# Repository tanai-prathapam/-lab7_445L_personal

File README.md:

## 0 Repository Structure

The typical explanation for the repo structure. Lab specific instructions can be
found further below.

### 0.1 HW

The `hw` folder should contain your schematic and board files for your PCB or
circuits. The ECE445L_Lab7 is the shared KiCad schematic for this lab and the final project (lab 10). 

### 0.2 SW

The `sw` folder should contain your application firmware and software written
for the lab. The `sw/inc` folder contains firmware drivers written for you by
Professor Valvano. Feel free to write your own (in fact, in some labs, you may
be required to write your own).

You can place any other source files in the `sw` folder. TAs will look at the
files you create and/or modify for software quality and for running your
project.

### 0.3 Resources

A couple files are provided in the Resources folder so you don't have to keep
searching for that one TI document. Some of them are immediately useful, like
the MSPM0 datasheet.

### 0.4 Git and Github

We will extensively use Git and Github for managing lab projects. This makes it
easier for TAs to grade and help debug the project by allowing us to see commit
histories, maintain a common project structure, and likewise, it makes it easier
for students to collaborate with partners, merge different codebases, and to
debug their work by having a history of commits.

Two common ways of using Git and Github are [Github Desktop](https://desktop.github.com/) and the [command line](https://git-scm.com/downloads).
[Tutorials](https://dev.to/mollynem/git-github--workflow-fundamentals-5496) are also abundant on the net for you to peruse. We've provided a cheatsheet for git
in the Resources folder.

It is highly recommended to make the most out of Git, even if you've never used
it before. Version control will save you a lot of suffering, and tools like Git
or SVN are ubiquitous in the industry.

A gitignore file is added to the root of this repo that may prevent specific
files from being tagged to the repo. This are typically autogenerated output
files we don't care about, but sometimes other stuff (like .lib files) falls
through that we want. Feel free to modify if necessary.

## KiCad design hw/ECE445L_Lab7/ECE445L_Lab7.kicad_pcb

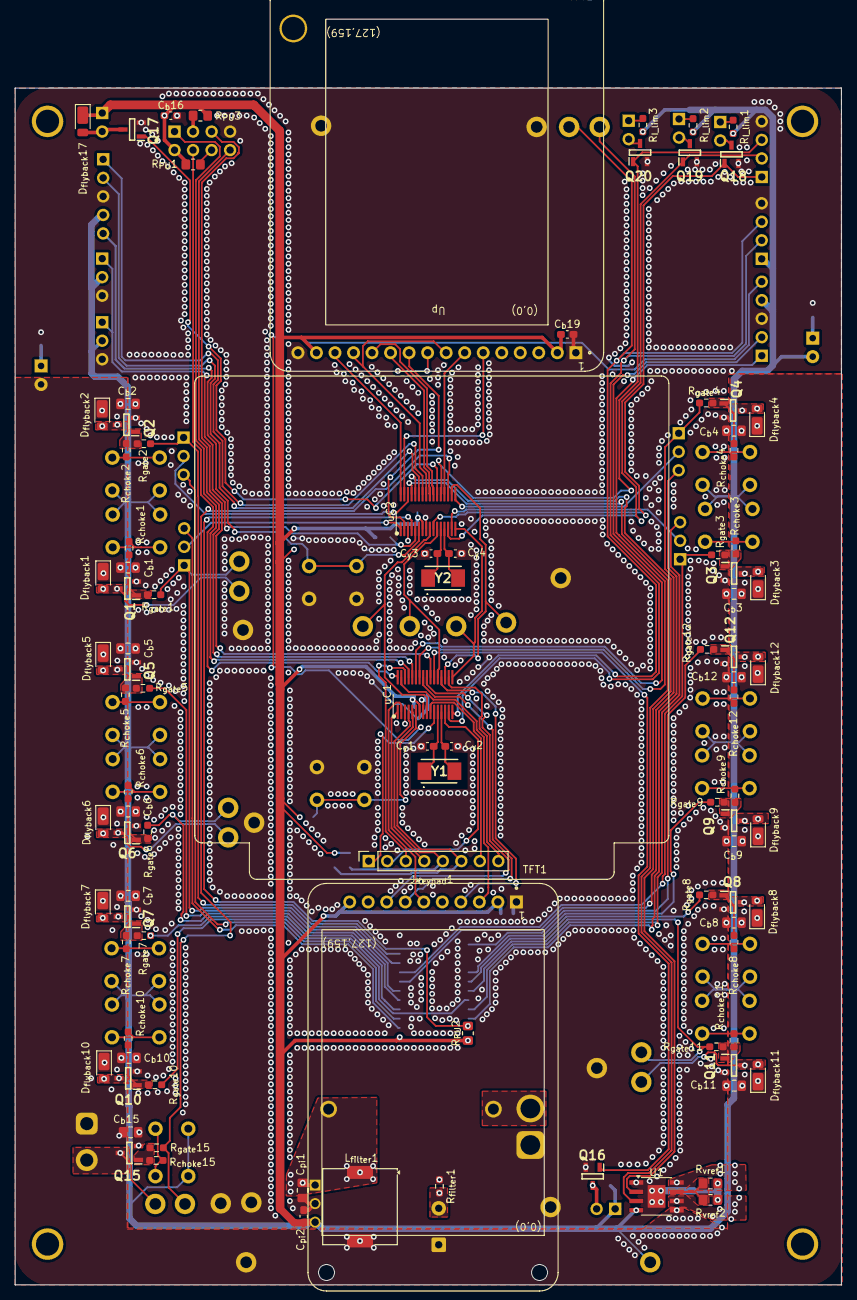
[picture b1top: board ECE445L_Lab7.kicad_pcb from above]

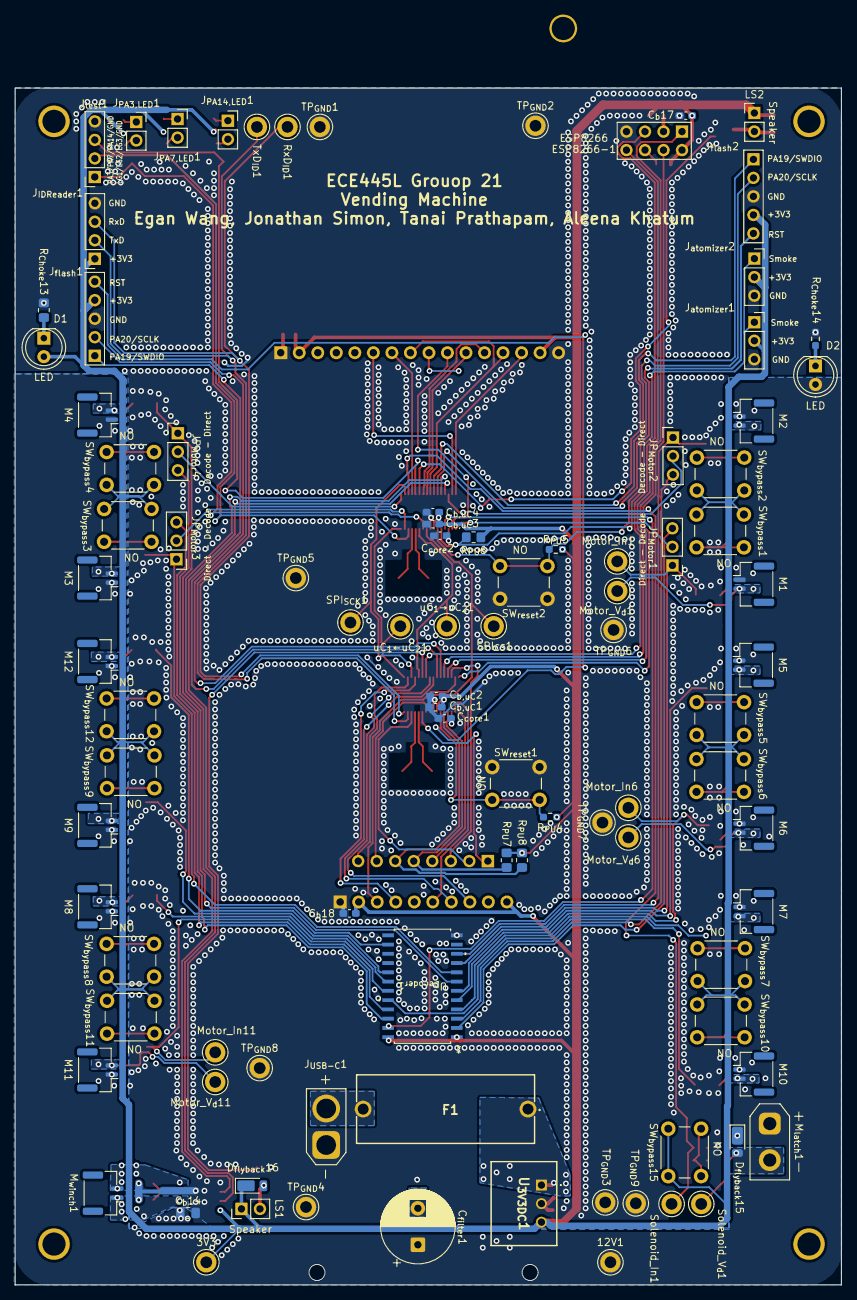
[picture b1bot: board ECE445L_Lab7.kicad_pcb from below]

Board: 2 copper layers, 113.3 x 164.1 mm, 195 parts (95 on the bottom side), 132 nets.

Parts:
3V3, 12V1: TestPoint; TestPoint_Keystone_5010-5014_Multipurpose
C_{b,uC}1, C_{b,uC}3: 100n; C_0603_1608Metric_Pad1.08x0.95mm_HandSolder
C_{b,uC}2, C_{b,uC}4: 10u; C_0603_1608Metric_Pad1.08x0.95mm_HandSolder
C_{b}1, C_{b}2, C_{b}3, C_{b}4, C_{b}5, C_{b}6, C_{b}7, C_{b}8, C_{b}9, C_{b}10, C_{b}11, C_{b}12, C_{b}14, C_{b}15: 4.7u; C_0805_2012Metric_Pad1.18x1.45mm_HandSolder
C_{b}16: 100n; C_0603_1608Metric_Pad1.08x0.95mm_HandSolder
C_{b}17, C_{b}18, C_{b}19: 4.7u; C_0603_1608Metric_Pad1.08x0.95mm_HandSolder
C_{core}1, C_{core}2: 0.47u; C_0603_1608Metric_Pad1.08x0.95mm_HandSolder
C_{filter}1: 1200u; CP_Radial_D10.0mm_P5.00mm
C_{pi}1: 4.7u; C_0805_2012Metric_Pad1.18x1.45mm_HandSolder
C_{pi}2: 4.7u; C_0603_1608Metric_Pad1.08x0.95mm_HandSolder
C_{y}1, C_{y}2, C_{y}3, C_{y}4: 10p; C_0603_1608Metric_Pad1.08x0.95mm_HandSolder
D1, D2: LED; LED_D5.0mm
D_{flyback}1, D_{flyback}2, D_{flyback}3, D_{flyback}4, D_{flyback}5, D_{flyback}6, D_{flyback}7, D_{flyback}8, D_{flyback}9, D_{flyback}10, D_{flyback}11, D_{flyback}12, D_{flyback}15, D_{flyback}16, D_{flyback}17: DFLS240LX-7; D_PowerDI-123
ESP8266: ESP8266-1; PinHeader_2x04_P2.54mm_Vertical
F1: Fuse; WR-FSH_THT_2
H1, H2, H3, H4: MountingHole_4_40
JP_{Motor}1, JP_{Motor}2, JP_{Motor}3, JP_{Motor}4: Jumper_3_Open; PinHeader_1x03_P2.54mm_Vertical
J_{IDReader}1: Conn_01x04; PinSocket_1x04_P2.54mm_Vertical
J_{Keypad}1: Conn_01x08; 4x4_Matrix_Keypad
J_{PA3,LED}1, J_{PA7,LED}1, J_{PA14,LED}1: Conn_01x02; PinSocket_1x02_P2.54mm_Vertical
J_{USB-C}1: Conn_01x02; AMASS_XT30U-M_1x02_P5.0mm_Vertical
J_{atomizer}1, J_{atomizer}2: Conn_01x03; PinSocket_1x03_P2.54mm_Vertical
J_{flash}1: J_{flash}1; PinHeader_1x05_P2.54mm_Vertical
J_{flash}2: J_{flash}2; PinHeader_1x05_P2.54mm_Vertical
J_{test}1: Conn_02x04_Counter_Clockwise; PinSocket_1x04_P2.54mm_Vertical
LS1, LS2: Speaker; PinHeader_1x02_P2.54mm_Vertical
L_{filter}1: 10uH; L_Coilcraft_MSS1038-XXX
M1, M2, M3, M4, M5, M6, M7, M8, M9, M10, M11, M12: Motor_DC; JST_GH_BM02B-GHS-TBT_1x02-1MP_P1.25mm_Vertical
M_{latch}1: Solenoid; AMASS_XT30UPB-F_1x02_P5.0mm_Vertical
M_{winch}1: Motor_DC; JST_GH_BM02B-GHS-TBT_1x02-1MP_P1.25mm_Vertical
Motor_In1, Motor_In6, Motor_In11: TestPoint; TestPoint_Keystone_5010-5014_Multipurpose
Motor_V_{d}1, Motor_V_{d}6, Motor_V_{d}11: TestPoint; TestPoint_Keystone_5010-5014_Multipurpose
Q1, Q2, Q3, Q4, Q5, Q6, Q7, Q8, Q9, Q10, Q11, Q12, Q15, Q16, Q17, Q18, Q19, Q20: NTR4501NT1G; SOT96P237X111-3N
R_{Choke}13: 10k; R_0805_2012Metric_Pad1.20x1.40mm_HandSolder
R_{Choke}14: 36.5k; R_0603_1608Metric_Pad0.98x0.95mm_HandSolder
R_{I_lim}1, R_{I_lim}2, R_{I_lim}3: R; R_0603_1608Metric_Pad0.98x0.95mm_HandSolder
R_{PU}1, R_{PU}2, R_{PU}3, R_{PU}6, R_{PU}7, R_{PU}8: 10k; R_0805_2012Metric_Pad1.20x1.40mm_HandSolder
R_{PU}4, R_{PU}5: 10k; R_0603_1608Metric_Pad0.98x0.95mm_HandSolder
R_{choke}1, R_{choke}2, R_{choke}3, R_{choke}4, R_{choke}5, R_{choke}6, R_{choke}7, R_{choke}8, R_{choke}9, R_{choke}10, R_{choke}11, R_{choke}12, R_{choke}15: 680; R_0603_1608Metric_Pad0.98x0.95mm_HandSolder
R_{filter}1: 0.25; R_0603_1608Metric_Pad0.98x0.95mm_HandSolder
R_{gate}1, R_{gate}2, R_{gate}3, R_{gate}4, R_{gate}5, R_{gate}6, R_{gate}7, R_{gate}8, R_{gate}9, R_{gate}10, R_{gate}11, R_{gate}12, R_{gate}15: 0.25; R_0603_1608Metric_Pad0.98x0.95mm_HandSolder
R_{vref}1, R_{vref}2: 264m; R_0805_2012Metric_Pad1.20x1.40mm_HandSolder
RxD_{ID}1: TestPoint; TestPoint_Keystone_5010-5014_Multipurpose
SPI_{CS}1: TestPoint; TestPoint_Keystone_5010-5014_Multipurpose
SPI_{SCK}1: TestPoint; TestPoint_Keystone_5010-5014_Multipurpose
SW_{bypass}1, SW_{bypass}2, SW_{bypass}3, SW_{bypass}4, SW_{bypass}5, SW_{bypass}6, SW_{bypass}7, SW_{bypass}8, SW_{bypass}9, SW_{bypass}10, SW_{bypass}11, SW_{bypass}12, SW_{bypass}15: NO; SW_PUSH_6mm
SW_{reset}1, SW_{reset}2: NO; SW_PUSH_6mm
Solenoid_In1: TestPoint; TestPoint_Keystone_5010-5014_Multipurpose
Solenoid_V_{d}1: TestPoint; TestPoint_Keystone_5010-5014_Multipurpose
TFT1: Adafruit ST7735R; adafruit_st7735r2
TFT2: HiLetGo_ST7735R; hiletgo_st7735r2
TP_{GND}1, TP_{GND}2, TP_{GND}3, TP_{GND}4, TP_{GND}5, TP_{GND}6, TP_{GND}7, TP_{GND}8, TP_{GND}9: TestPoint; TestPoint_Keystone_5010-5014_Multipurpose
TxD_{ID}1: TestPoint; TestPoint_Keystone_5010-5014_Multipurpose
U1: DRV8231ADSG; TI_SO-PowerPAD-8
U_{3V3DC}1: N7803-2C; N78032C
U_{Decoder}1: MC14514BDWR2G; SOIC-24WB_ONS
Y1, Y2: 16MHz; ABM3
uC1, uC2: M0G3507QDGS32RQ1; VSSOP_0.5mm_32pin_handsolder
uC_{1}←uC_{2}1, uC_{1}→uC_{2}1: TestPoint; TestPoint_Keystone_5010-5014_Multipurpose

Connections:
+3V3: 3V3.1 (1_1), C_{b,uC}1.1, C_{b,uC}2.1, C_{b,uC}3.1, C_{b,uC}4.1, C_{b}16.1, C_{b}17.1, C_{b}18.1, C_{b}19.1, C_{pi}2.1, D1.2 (A), D_{flyback}16.1 (K), D_{flyback}17.1 (K), ESP8266.8 (Vcc), J_{IDReader}1.1, J_{atomizer}1.2, J_{atomizer}2.2, J_{flash}1.4 (C), J_{flash}2.4 (C), LS1.1, LS2.1, R_{I_lim}1.1, R_{I_lim}2.1, R_{I_lim}3.1, R_{PU}1.1, R_{PU}2.1, R_{PU}3.1, R_{PU}4.1, R_{PU}5.1, R_{PU}6.1, R_{PU}7.1, R_{PU}8.1, SW_{bypass}1.1, SW_{bypass}2.1, SW_{bypass}3.1, SW_{bypass}4.1, SW_{bypass}5.1, SW_{bypass}6.1, SW_{bypass}7.1, SW_{bypass}8.1, SW_{bypass}9.1, SW_{bypass}10.1, SW_{bypass}11.1, SW_{bypass}12.1, SW_{bypass}15.1, TFT1.2 (VCC), TFT1.10 (LITE), TFT2.2 (VCC), TFT2.15 (LED+), U1.4 (VREF), U_{3V3DC}1.3 (Vout), U_{Decoder}1.1 (ST), U_{Decoder}1.24 (VDD), uC1.7 (VDD), uC2.7 (VDD)
+12V: 12V1.1 (1_1), C_{b}1.1, C_{b}2.1, C_{b}3.1, C_{b}4.1, C_{b}5.1, C_{b}6.1, C_{b}7.1, C_{b}8.1, C_{b}9.1, C_{b}10.1, C_{b}11.1, C_{b}12.1, C_{b}14.1, C_{b}15.1, C_{filter}1.1, D2.2 (A), D_{flyback}1.1 (K), D_{flyback}2.1 (K), D_{flyback}3.1 (K), D_{flyback}4.1 (K), D_{flyback}5.1 (K), D_{flyback}6.1 (K), D_{flyback}7.1 (K), D_{flyback}8.1 (K), D_{flyback}9.1 (K), D_{flyback}10.1 (K), D_{flyback}11.1 (K), D_{flyback}12.1 (K), D_{flyback}15.1 (K), L_{filter}1.2, M1.1 (+), M2.1 (+), M3.1 (+), M4.1 (+), M5.1 (+), M6.1 (+), M7.1 (+), M8.1 (+), M9.1 (+), M10.1 (+), M11.1 (+), M12.1 (+), M_{latch}1.1 (+), U1.5 (VM)
/Lab7 Electromech/V_{d,motor 1}: D_{flyback}1.2 (A), M1.2 (-), Motor_V_{d}1.1 (1_1), Q1.3 (D)
/Lab7 Electromech/V_{d,motor 2}: D_{flyback}2.2 (A), M2.2 (-), Q2.3 (D)
/Lab7 Electromech/V_{d,motor 3}: D_{flyback}3.2 (A), M3.2 (-), Q3.3 (D)
/Lab7 Electromech/V_{d,motor 4}: D_{flyback}4.2 (A), M4.2 (-), Q4.3 (D)
/Lab7 Electromech/V_{d,motor 5}: D_{flyback}5.2 (A), M5.2 (-), Q5.3 (D)
/Lab7 Electromech/V_{d,motor 6}: D_{flyback}6.2 (A), M6.2 (-), Motor_V_{d}6.1 (1_1), Q6.3 (D)
/Lab7 Electromech/V_{d,motor 7}: D_{flyback}7.2 (A), M7.2 (-), Q7.3 (D)
/Lab7 Electromech/V_{d,motor 8}: D_{flyback}8.2 (A), M8.2 (-), Q8.3 (D)
/Lab7 Electromech/V_{d,motor 9}: D_{flyback}9.2 (A), M9.2 (-), Q9.3 (D)
/Lab7 Electromech/V_{d,motor 10}: D_{flyback}10.2 (A), M10.2 (-), Q10.3 (D)
/Lab7 Electromech/V_{d,motor 11}: D_{flyback}11.2 (A), M11.2 (-), Motor_V_{d}11.1 (1_1), Q11.3 (D)
/Lab7 Electromech/V_{d,motor 12}: D_{flyback}12.2 (A), M12.2 (-), Q12.3 (D)
/Lab7 Electromech/V_{d,solenoid}: D_{flyback}15.2 (A), M_{latch}1.2 (-), Q15.3 (D), Solenoid_V_{d}1.1 (1_1)
/Lab7 IO/D_{Motor}1: JP_{Motor}1.3 (B), U_{Decoder}1.2 (D1)
/Lab7 IO/D_{Motor}2: JP_{Motor}2.3 (B), U_{Decoder}1.3 (D2)
/Lab7 IO/D_{Motor}3: JP_{Motor}3.3 (B), U_{Decoder}1.21 (D3)
/Lab7 IO/D_{Motor}4: JP_{Motor}4.3 (B), U_{Decoder}1.22 (D4)
/Lab7 Microcontroller/uC SPI - uC_{1} ← uC_{2}: uC1.17 (PA10/CLK_OUT), uC2.16 (PA9/RTC_OUT/CLK_OUT), uC_{1}←uC_{2}1.1 (1_1)
/Lab7 Microcontroller/uC SPI - uC_{1} → uC_{2}: uC1.21 (PA14/CLK_OUT/A0_12), uC2.11 (PA4/LFCLK_IN/LFXOUT), uC_{1}→uC_{2}1.1 (1_1)
/Lab7 Microcontroller/uC_{1} - RST: J_{flash}1.5 (C), R_{PU}4.2, SW_{reset}1.2, uC1.6 (NRST)
/Lab7 Microcontroller/uC_{1} - SWCLK: J_{flash}1.2 (B), uC1.27 (PA20/SWCLK)
/Lab7 Microcontroller/uC_{1} - SWDIO: J_{flash}1.1 (A), uC1.26 (PA19/SWDIO)
/Lab7 Microcontroller/uC_{1} - V_{core}: C_{core}1.1, uC1.3 (VCORE)
/Lab7 Microcontroller/uC_{2} - RST: J_{flash}2.5 (C), R_{PU}5.2, SW_{reset}2.2, uC2.6 (NRST)
/Lab7 Microcontroller/uC_{2} - SWCLK: J_{flash}2.2 (B), uC2.27 (PA20/SWCLK)
/Lab7 Microcontroller/uC_{2} - SWDIO: J_{flash}2.1 (A), uC2.26 (PA19/SWDIO)
/Lab7 Microcontroller/uC_{2} - V_{core}: C_{core}2.1, uC2.3 (VCORE)
/Lab7 Power/V_{in,fused}: C_{pi}1.1, F1.1, L_{filter}1.1, U_{3V3DC}1.1 (Vin)
/Lab7 Power/V_{in}: F1.2, J_{USB-C}1.2
Adafruit - CS: TFT1.6 (TFT_CS), uC1.2 (PA27/RTC_OUT/A0_0)
Adafruit - D/C: TFT1.4 (D/C), uC1.20 (PA13)
Adafruit - MOSI: TFT1.7 (MOSI), uC1.25 (PA18/A1_3)
Adafruit - RST: TFT1.3 (RESET), uC1.31 (PA24/A0_3)
Adafruit - SCK: TFT1.8 (SCK), uC1.24 (PA17/A1_2)
GND: C_{b,uC}1.2, C_{b,uC}2.2, C_{b,uC}3.2, C_{b,uC}4.2, C_{b}1.2, C_{b}2.2, C_{b}3.2, C_{b}4.2, C_{b}5.2, C_{b}6.2, C_{b}7.2, C_{b}8.2, C_{b}9.2, C_{b}10.2, C_{b}11.2, C_{b}12.2, C_{b}14.2, C_{b}15.2, C_{b}16.2, C_{b}17.2, C_{b}18.2, C_{b}19.2, C_{core}1.2, C_{core}2.2, C_{pi}1.2, C_{pi}2.2, C_{y}1.2, C_{y}2.2, C_{y}3.2, C_{y}4.2, ESP8266.4 (GND), J_{IDReader}1.4, J_{USB-C}1.1, J_{atomizer}1.3, J_{atomizer}2.3, J_{flash}1.3 (C), J_{flash}2.3 (C), J_{test}1.4, Q1.2 (S), Q2.2 (S), Q3.2 (S), Q4.2 (S), Q5.2 (S), Q6.2 (S), Q7.2 (S), Q8.2 (S), Q9.2 (S), Q10.2 (S), Q11.2 (S), Q12.2 (S), Q15.2 (S), Q16.2 (S), Q17.2 (S), Q18.2 (S), Q19.2 (S), Q20.2 (S), R_{Choke}13.2, R_{Choke}14.2, R_{filter}1.2, R_{vref}1.2, R_{vref}2.2, SW_{reset}1.1, SW_{reset}2.1, TFT1.1 (GND), TFT2.1 (GND), TFT2.16 (LED-), TP_{GND}1.1 (1_1), TP_{GND}2.1 (1_1), TP_{GND}3.1 (1_1), TP_{GND}4.1 (1_1), TP_{GND}5.1 (1_1), TP_{GND}6.1 (1_1), TP_{GND}7.1 (1_1), TP_{GND}8.1 (1_1), TP_{GND}9.1 (1_1), U1.1 (GND), U1.9 (GND), U_{3V3DC}1.2 (GND), U_{Decoder}1.12 (VSS), uC1.8 (VSS), uC2.8 (VSS)
HLG SDC - CS: TFT2.14 (SDC_CS), uC2.32 (PA25/A0_2)
HLG SDC - MISO: TFT2.12 (SDC_MISO), uC2.23 (PA16/A1_1/FCC_IN)
HLG Screen - CS: TFT2.10 (TFT_CS), uC2.2 (PA27/RTC_OUT/A0_0)
HLG Screen - D/C: TFT2.7 (TFTDC), uC2.20 (PA13)
HLG Screen - MOSI: TFT2.8 (TFTMOSI), TFT2.13 (SDC_MOSI), uC2.25 (PA18/A1_3)
HLG Screen- RST: TFT2.6 (RESET), uC2.31 (PA24/A0_3)
HiLetGo - SCK: TFT2.9 (TFTSCK), TFT2.11 (SDCSCK), uC2.24 (PA17/A1_2)
ID Scan - RxD: J_{IDReader}1.3, RxD_{ID}1.1 (1_1), uC1.16 (PA9/RTC_OUT/CLK_OUT)
ID Scan - TxD: J_{IDReader}1.2, TxD_{ID}1.1 (1_1), uC1.15 (PA8)
Keypad - C1: J_{Keypad}1.5, R_{PU}7.2, uC1.4 (PA0)
Keypad - C2: J_{Keypad}1.6, R_{PU}8.2, uC1.5 (PA1)
Keypad - C3: J_{Keypad}1.7, uC1.10 (PA3/LFXIN)
Keypad - C4: J_{Keypad}1.8, uC1.18 (PA11)
Keypad - R1: J_{Keypad}1.1, uC1.11 (PA4/LFCLK_IN/LFXOUT)
Keypad - R2: J_{Keypad}1.2, uC1.14 (PA7/CLK_OUT)
Keypad - R3: J_{Keypad}1.3, uC1.30 (PA23/VREF+)
Keypad - R4: J_{Keypad}1.4, uC1.1 (PA26/A0_1)
Motor PWM: R_{PU}2.2, U_{Decoder}1.23 (INH), uC2.4 (PA0)
Motor_{1}: JP_{Motor}1.1 (A), Motor_In1.1 (1_1), R_{gate}1.2, U_{Decoder}1.9 (S1)
Motor_{2}: JP_{Motor}2.1 (A), R_{gate}2.2, U_{Decoder}1.10 (S2)
Motor_{3}: JP_{Motor}3.1 (A), R_{gate}3.2, U_{Decoder}1.8 (S3)
Motor_{4}: JP_{Motor}4.1 (A), R_{gate}4.2, U_{Decoder}1.7 (S4)
Motor_{5}: R_{gate}5.2, U_{Decoder}1.6 (S5)
Motor_{6}: Motor_In6.1 (1_1), R_{gate}6.2, U_{Decoder}1.5 (S6)
Motor_{7}: R_{gate}7.2, U_{Decoder}1.4 (S7)
Motor_{8}: R_{gate}8.2, U_{Decoder}1.18 (S8)
Motor_{9}: R_{gate}9.2, U_{Decoder}1.17 (S9)
Motor_{10}: R_{gate}10.2, U_{Decoder}1.20 (S10)
Motor_{11}: Motor_In11.1 (1_1), R_{gate}11.2, U_{Decoder}1.19 (S11)
Motor_{12}: R_{gate}12.2, U_{Decoder}1.14 (S12)
unnamed: C_{filter}1.2, R_{filter}1.1
unnamed: D1.1 (K), R_{Choke}13.1
unnamed: D2.1 (K), R_{Choke}14.1
unnamed: D_{flyback}16.2 (A), LS1.2, Q16.3 (D)
unnamed: D_{flyback}17.2 (A), LS2.2, Q17.3 (D)
unnamed: ESP8266.6 (Ch_PD), R_{PU}1.2
unnamed: ESP8266.2 (GPIO0), R_{PU}3.2
unnamed: J_{PA3,LED}1.1, R_{I_lim}1.2
unnamed: J_{PA3,LED}1.2, Q18.3 (D)
unnamed: J_{PA7,LED}1.1, R_{I_lim}2.2
unnamed: J_{PA7,LED}1.2, Q19.3 (D)
unnamed: J_{PA14,LED}1.1, R_{I_lim}3.2
unnamed: J_{PA14,LED}1.2, Q20.3 (D)
unnamed: M_{winch}1.1 (+), U1.6 (OUT1)
unnamed: M_{winch}1.2 (-), U1.8 (OUT2)
unnamed: Q1.1 (G), R_{choke}1.1, R_{gate}1.1
unnamed: Q2.1 (G), R_{choke}2.1, R_{gate}2.1
unnamed: Q3.1 (G), R_{choke}3.1, R_{gate}3.1
unnamed: Q4.1 (G), R_{choke}4.1, R_{gate}4.1
unnamed: Q5.1 (G), R_{choke}5.1, R_{gate}5.1
unnamed: Q6.1 (G), R_{choke}6.1, R_{gate}6.1
unnamed: Q7.1 (G), R_{choke}7.1, R_{gate}7.1
unnamed: Q8.1 (G), R_{choke}8.1, R_{gate}8.1
unnamed: Q9.1 (G), R_{choke}9.1, R_{gate}9.1
unnamed: Q10.1 (G), R_{choke}10.1, R_{gate}10.1
unnamed: Q11.1 (G), R_{choke}11.1, R_{gate}11.1
unnamed: Q12.1 (G), R_{choke}12.1, R_{gate}12.1
unnamed: Q15.1 (G), R_{choke}15.1, R_{gate}15.1
unnamed: R_{choke}1.2, SW_{bypass}1.2
unnamed: R_{choke}2.2, SW_{bypass}2.2
unnamed: R_{choke}3.2, SW_{bypass}3.2
unnamed: R_{choke}4.2, SW_{bypass}4.2
unnamed: R_{choke}5.2, SW_{bypass}5.2
unnamed: R_{choke}6.2, SW_{bypass}6.2
unnamed: R_{choke}7.2, SW_{bypass}7.2
unnamed: R_{choke}8.2, SW_{bypass}8.2
unnamed: R_{choke}9.2, SW_{bypass}9.2
unnamed: R_{choke}10.2, SW_{bypass}10.2
unnamed: R_{choke}11.2, SW_{bypass}11.2
unnamed: R_{choke}12.2, SW_{bypass}12.2
unnamed: R_{choke}15.2, SW_{bypass}15.2
unnamed: R_{vref}1.1, R_{vref}2.1, U1.7 (IPROPI)
PA3/LG1: J_{test}1.1, Q18.1 (G), uC2.10 (PA3/LFXIN)
PA7/LG2: J_{test}1.2, Q19.1 (G), uC2.14 (PA7/CLK_OUT)
PA14/LG3: J_{test}1.3, Q20.1 (G), uC2.21 (PA14/CLK_OUT/A0_12)
Smoke: J_{atomizer}1.1, J_{atomizer}2.1, R_{PU}6.2, uC2.5 (PA1)
Solenoid: R_{gate}15.2, Solenoid_In1.1 (1_1), uC2.19 (PA12/FCC_IN)
Winch_{1}: U1.3 (IN1), uC2.29 (PA22/CLK_OUT/A0_7)
Winch_{2}: U1.2 (IN2), uC2.28 (PA21/A1_7/VREF-)
uC SPI - CS: SPI_{CS}1.1 (1_1), uC1.9 (PA2/ROSC), uC2.9 (PA2/ROSC)
uC SPI - SCK: SPI_{SCK}1.1 (1_1), uC1.19 (PA12/FCC_IN), uC2.18 (PA11)
uC_{1} - ESP Light: ESP8266.3 (GPIO2), uC1.23 (PA16/A1_1/FCC_IN)
uC_{1} - ESP RST: ESP8266.7 (Reset), uC1.32 (PA25/A0_2)
uC_{1} - ESP RxD: ESP8266.1 (RxD), uC1.29 (PA22/CLK_OUT/A0_7)
uC_{1} - ESP TxD: ESP8266.5 (TxD), uC1.28 (PA21/A1_7/VREF-)
uC_{1} - HFXIN: C_{y}1.1, Y1.1, uC1.12 (PA5/HFXIN/FCC_IN)
uC_{1} - HFXOUT: C_{y}2.1, Y1.2, uC1.13 (PA6/HFCLK_IN/HFXOUT)
uC_{1} - Speaker: Q16.1 (G), uC1.22 (PA15/A1_0/DACOUT)
uC_{2} - HFXIN: C_{y}3.1, Y2.1, uC2.12 (PA5/HFXIN/FCC_IN)
uC_{2} - HFXOUT: C_{y}4.1, Y2.2, uC2.13 (PA6/HFCLK_IN/HFXOUT)
uC_{2} - Motor_{1}: JP_{Motor}1.2 (C), uC2.1 (PA26/A0_1)
uC_{2} - Motor_{2}: JP_{Motor}2.2 (C), uC2.30 (PA23/VREF+)
uC_{2} - Motor_{3}: JP_{Motor}3.2 (C), uC2.15 (PA8)
uC_{2} - Motor_{4}: JP_{Motor}4.2 (C), uC2.17 (PA10/CLK_OUT)
uC_{2} - Speaker: Q17.1 (G), uC2.22 (PA15/A1_0/DACOUT)
